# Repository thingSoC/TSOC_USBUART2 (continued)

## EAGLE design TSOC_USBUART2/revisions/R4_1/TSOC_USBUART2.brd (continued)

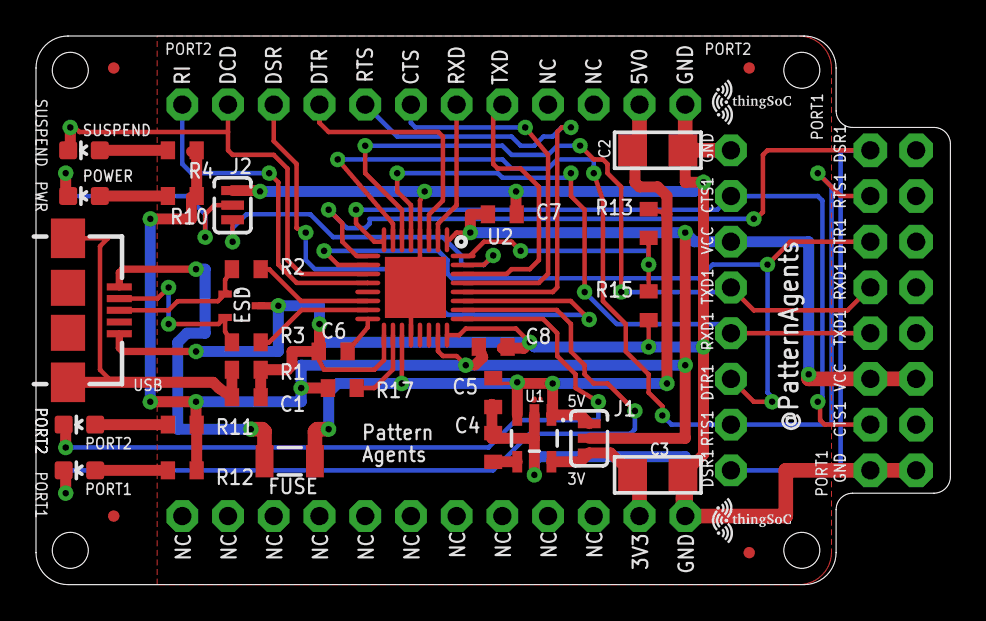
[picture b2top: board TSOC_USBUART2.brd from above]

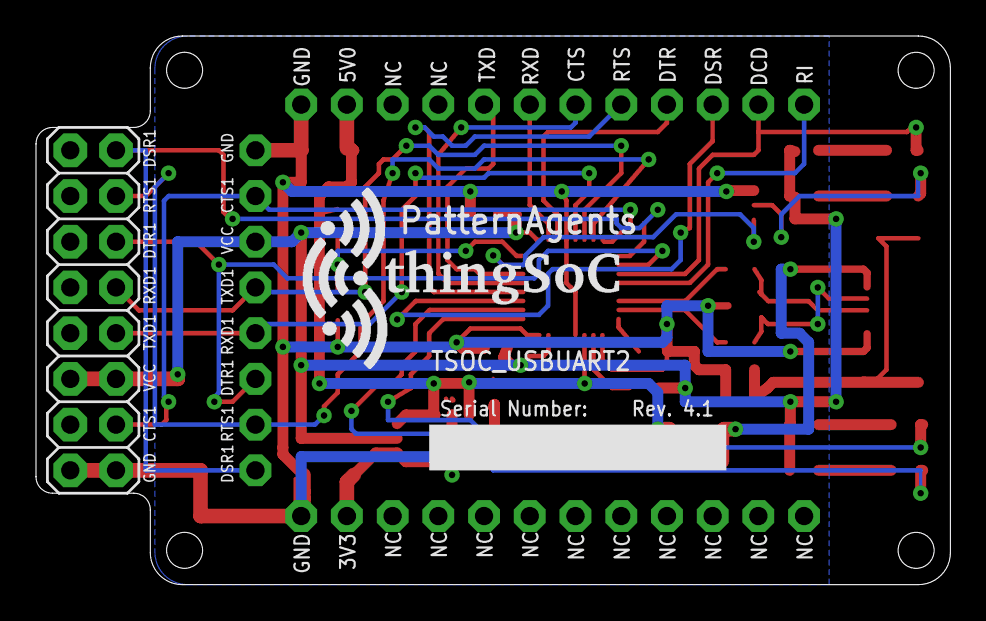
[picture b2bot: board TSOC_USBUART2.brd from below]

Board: 2 copper layers, 50.8 x 30.5 mm, 42 parts (2 on the bottom side), 36 nets.

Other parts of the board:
U$1: TSOC-LOGO-SMALL; TSOC-LOGO-SML

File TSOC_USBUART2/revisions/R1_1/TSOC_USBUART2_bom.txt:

Partlist exported from /home/moxon/github/TSOC-USBUART2/TSOC-USBUART2/TSOC_USBUART2.sch at 4/9/16 11:58 AM
Qty Value              Device             Package          Parts                  Description
1   RED                LED0603            LED-0603         SUSPEND                LEDs                                                            
1   GRN                LED0603            LED-0603         POWER                  LEDs                                                                 
1   BLUE               LED0603            LED-0603         TXD                    LEDs                          
1   YELLOW             LED0603            LED-0603         RXD                    LEDs
3   0.1uF              CAP-0603           EIA-0603         C5, C7, C8             Ceramic Capacitor SMD
1   1.0uF              CAP-0603           EIA-0603         C6                     Ceramic Capacitor SMD
2   10K                RESISTOR-0603      EIA-0603         R15, R17                                   
1   1A                 FUSE               EIA-0603         F1                     Resettable PPTC Fuse - 0603 Footptint
4   1K                 RESISTOR-0603      EIA-0603         R4, R10, R11, R12                                          
1   1M                 RESISTOR-0603      EIA-0603         R1                                                        
2   22                 RESISTOR-0603      EIA-0603         R2, R3                                                   
1   22K                RESISTOR-0603      EIA-0603         R13                                                     
2   22uF               CAP-1206           EIA-1206         C2, C3                 Ceramic Capacitor SMD           
2   470pF              CAP-0603           EIA-0603         C1, C4                 Ceramic Capacitor SMD          
1   CY7C65215-32-PROTO CY7C65215-32-PROTO QFN32-PROTO      U2                     Cypress EZ-USB ® CY7C65215-32QFN DUAL CHANNEL USB TO UART/SPI/IC Bridge
1   M08                M08                1X08-SMD-FEMALE  P1                                                                                        
1   M08PTH             M08PTH             1X08             P1A                                                                                      
1   MIC5219 3.3V       V_REG_MIC52193.3V  SOT23-5          U1                     V_REG MIC5219                                                    
1   SP1001-02JTG       SP1001-02JTG       SC70-3           ESD                    Littelfuse SP1001-02JTG TVS Diode Array 8pf 15kV 
1   USB_AB             USB_AB             USB-AB-MICRO-SMD USB                    USB AB connector

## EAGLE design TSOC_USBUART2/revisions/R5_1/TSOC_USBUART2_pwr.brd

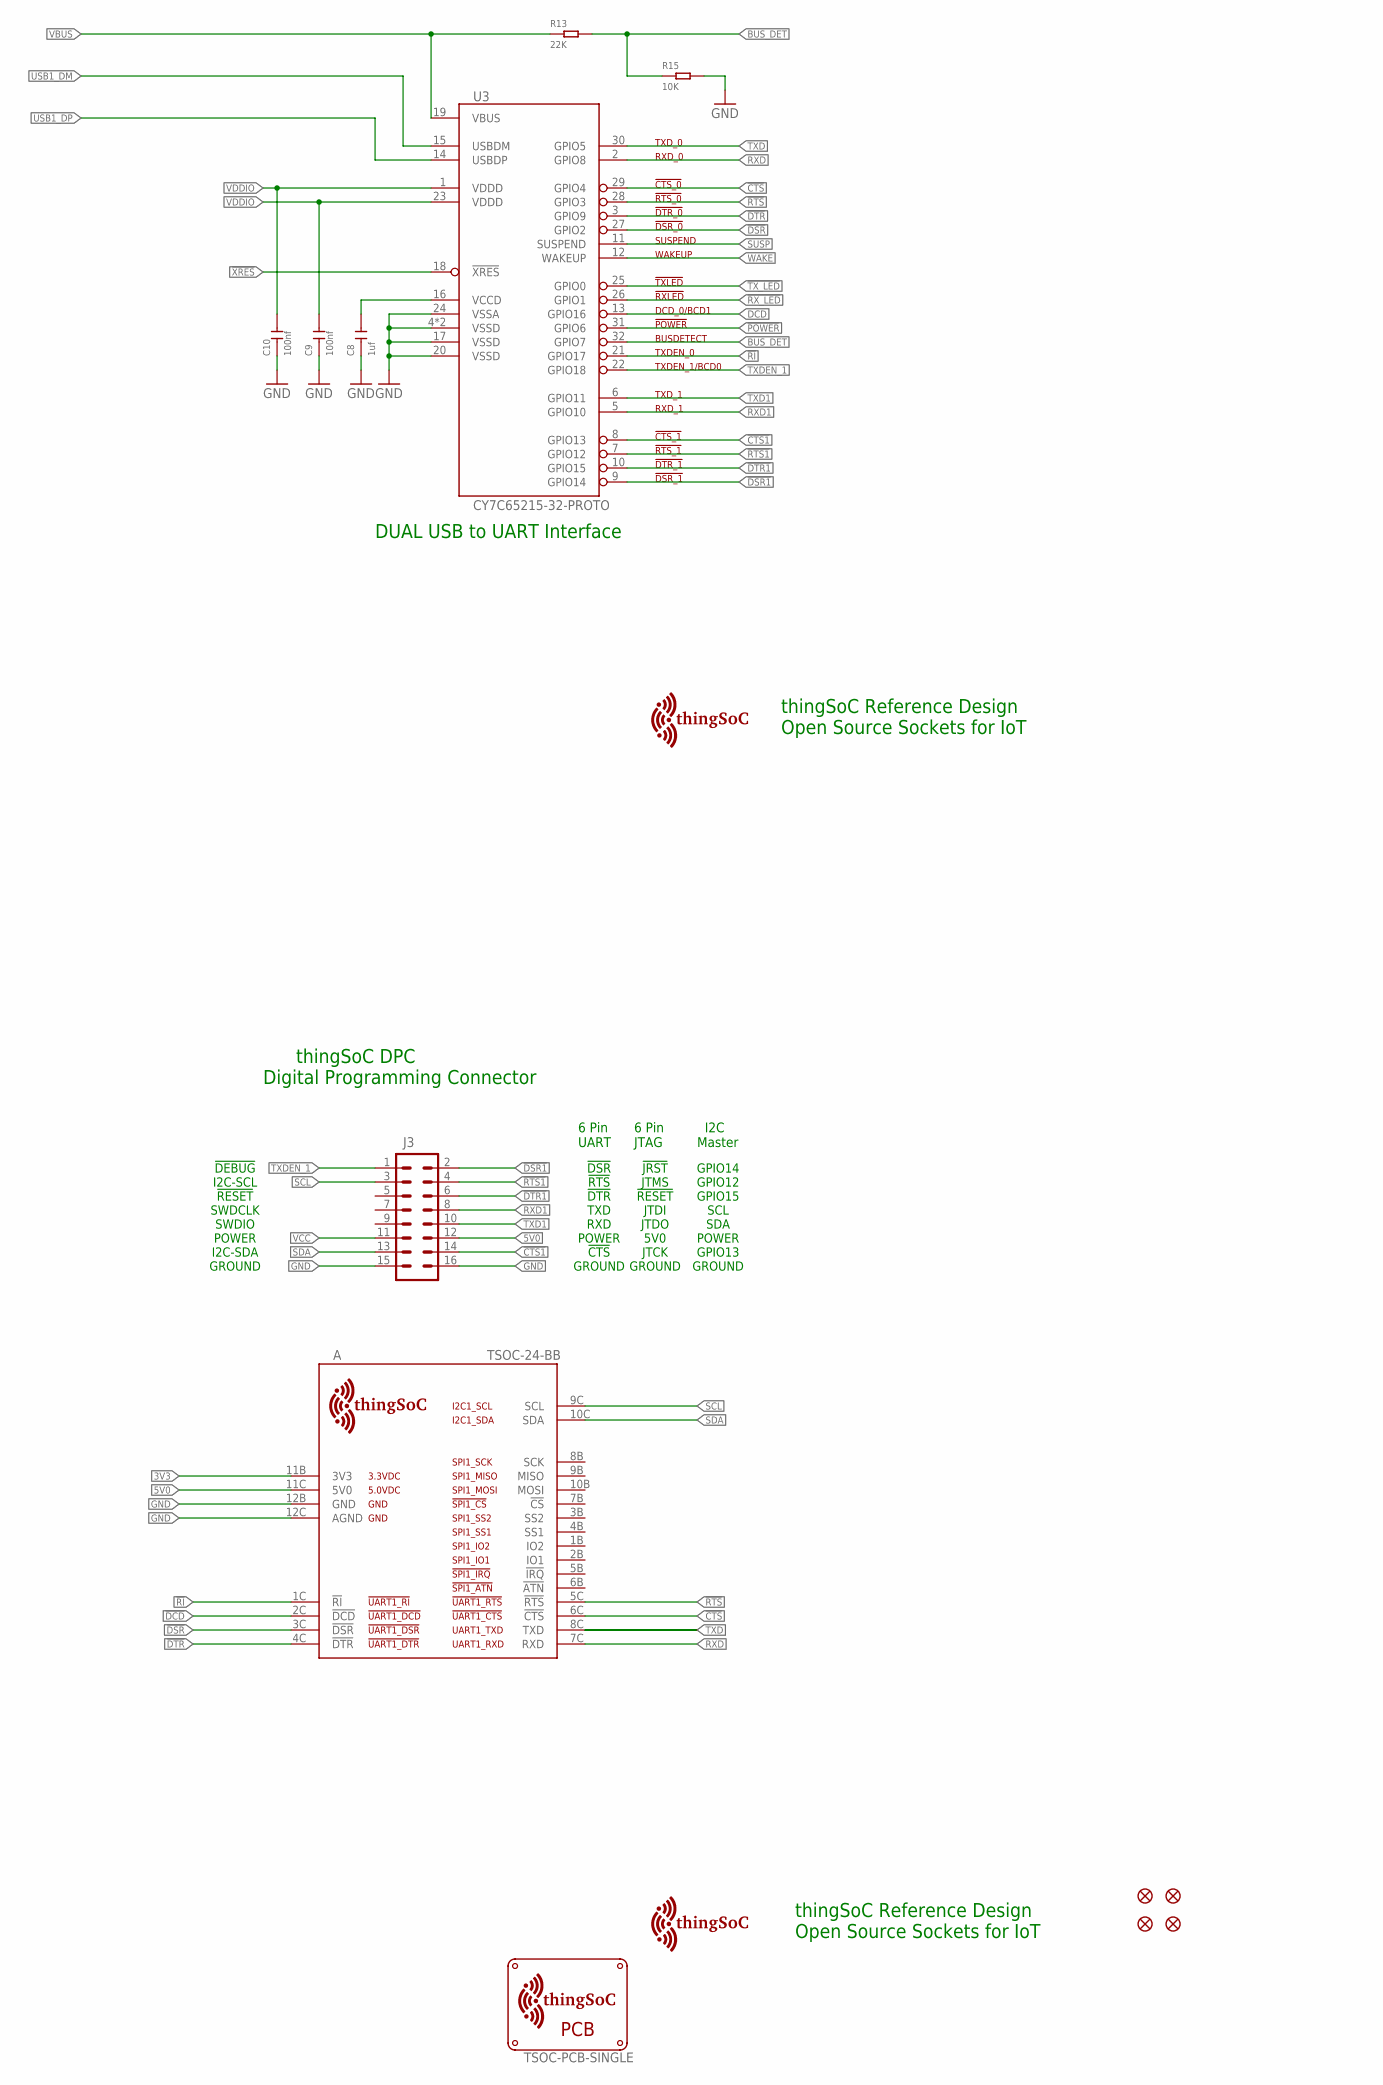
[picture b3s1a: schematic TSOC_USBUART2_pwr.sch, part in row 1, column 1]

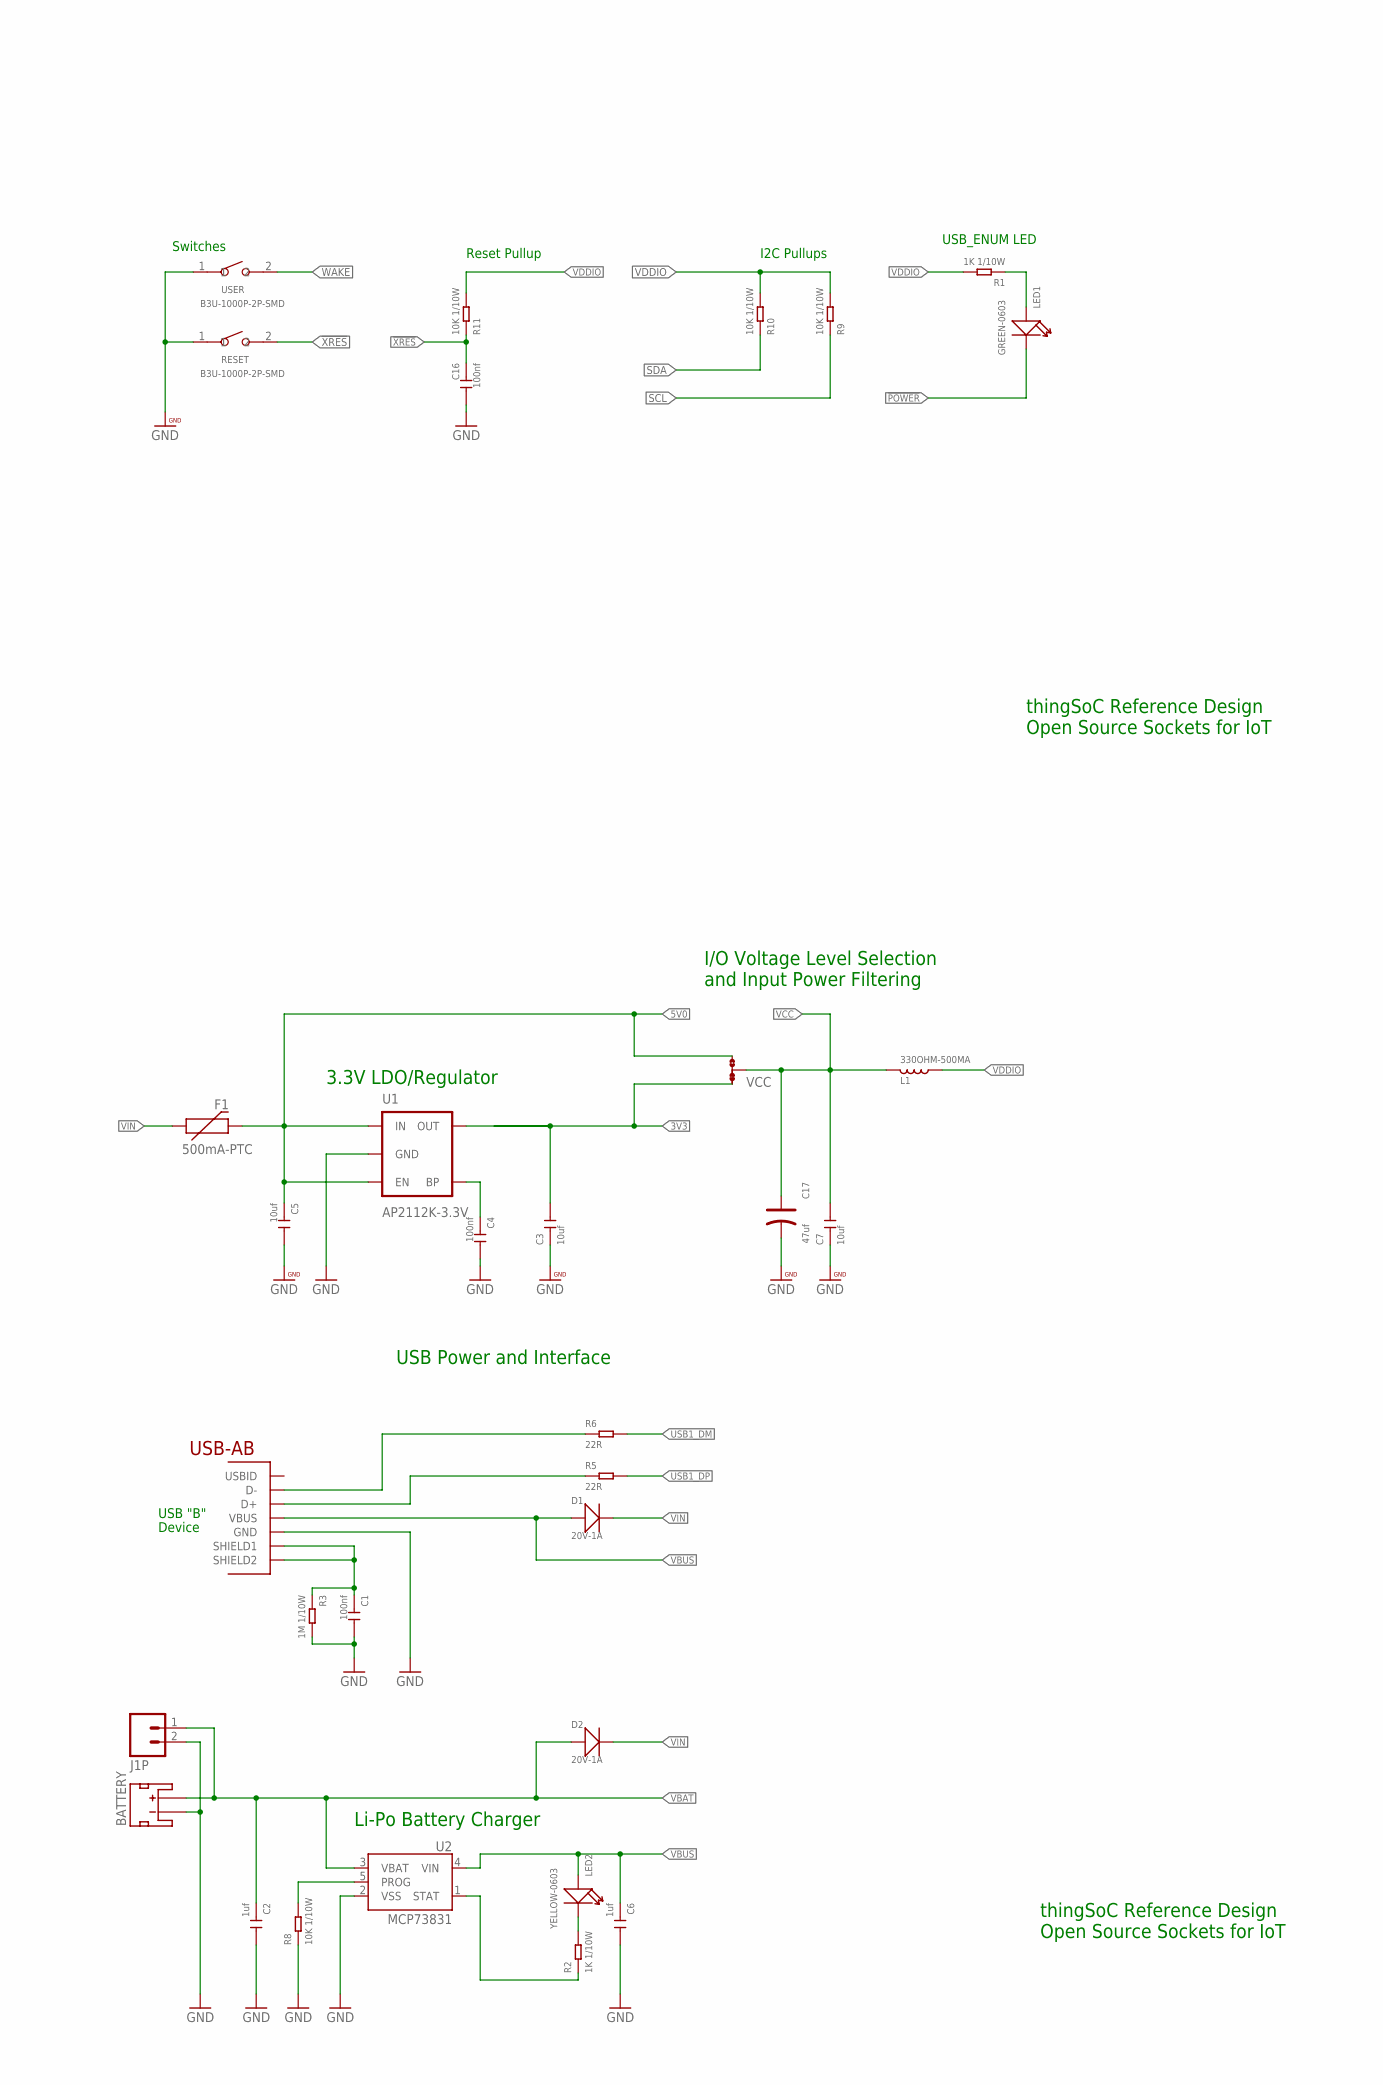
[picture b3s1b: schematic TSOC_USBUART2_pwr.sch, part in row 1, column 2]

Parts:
A: TSOC-24-BB; TSOC-BB-S24
BATTERY: JST_2MM_MALE; JST-2-SMD
C1, C4, C9, C10, C16: 100nf; C0603
C2, C6, C8: 1uf; C0603
C3, C5, C7: 10uf; C0603
C17: 47uf; AVX-A
D1, D2: 20V-1A; SOD-123
F1: 500mA-PTC; PTC-1206
FID1, FID2, FID3, FID4: FIDUCIALUFIDUCIAL; MICRO-FIDUCIAL
J1P: M02-JST-2-PTH-NO_SILK; JST-2-PTH-NS
J3: M08X2; 2X8
L1: 330OHM-500MA; L0603
LED1: GREEN-0603; LED-0603
LED2: YELLOW-0603; LED-0603
R1, R2: 1K 1/10W; R0603
R3: 1M 1/10W; R0603
R5, R6: 22R; R0603
R8, R9, R10, R11: 10K 1/10W; R0603
R13: 22K; R0603
R15: 10K; R0603
RESET: B3U-1000P-2P-SMD; SW2-2.6-3.0X2.5X1.2+0.4MM
U1: AP2112K-3.3V; SOT23-5
U2: MCP73831; SOT23-5
U3: CY7C65215-32-PROTO; QFN32-PROTO
U$1: TSOC-PCB-SINGLE; TSOC-BB-BRD-DIM
U$100: TSOC-LOGO-LRG
U$101: TSOC-LOGO-SMALL; TSOC-LOGO-SML
USB: USB_AB; USB-AB-MICRO-SMD
USER: B3U-1000P-2P-SMD; SW2-2.6-3.0X2.5X1.2+0.4MM
VCC: JMP-3-1_2

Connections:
3V3: A.11B (3V3), C3.2, U1.5 (OUT), VCC.1
5V0: A.11C (5V0), C5.1, F1.2, J3.12, U1.1 (IN), U1.3 (EN), VCC.3
!CTS: A.6C (!CTS), U3.29 (GPIO4)
!CTS1: J3.14, U3.8 (GPIO13)
!DCD: A.2C (!DCD)
!DSR: A.3C (!DSR), U3.27 (GPIO2)
!DSR1: J3.2, U3.9 (GPIO14)
!DTR: A.4C (!DTR), U3.3 (GPIO9)
!DTR1: J3.6, U3.10 (GPIO15)
!POWER: LED1.-, U3.31 (GPIO6)
!RI: A.1C (!RI), U3.21 (GPIO17)
!RTS: A.5C (!RTS), U3.28 (GPIO3)
!RTS1: J3.4, U3.7 (GPIO12)
!RX_LED: U3.26 (GPIO1)
!TX_LED: U3.25 (GPIO0)
!XRES: C16.1, R11.1, RESET.2, U3.18 (!XRES)
BUS_DET: R13.2, R15.1, U3.32 (GPIO7)
BYPASS1: C4.1, U1.4 (BP)
CLED: LED2.-, R2.2
CSTAT: R2.1, U2.1 (STAT)
DCD: U3.13 (GPIO16)
GND: A.12B (GND), A.12C (AGND), BATTERY.1 (-), C1.2, C2.2, C3.1, C4.2, C5.2, C6.2, C7.1, C8.1, C9.1, C10.1, C16.2, C17.-, J1P.2, J3.15, J3.16, R3.2, R8.1, R15.2, RESET.1, U1.2 (GND), U2.2 (VSS), U3.4 (VSSD), U3.17 (VSSD), U3.20 (VSSD), U3.24 (VSSA), U3.EXP (VSSD), USB.GND, USER.1
unnamed: R8.2, U2.5 (PROG)
unnamed: LED1.+, R1.1
RXD: A.7C (RXD), U3.2 (GPIO8)
RXD1: J3.8, U3.5 (GPIO10)
SCL: A.9C (SCL), J3.3, R9.1
SDA: A.10C (SDA), J3.13, R10.1
SUSP: U3.11 (SUSPEND)
TXD: A.8C (TXD), U3.30 (GPIO5)
TXD1: J3.10, U3.6 (GPIO11)
TXDEN_1: J3.1, U3.22 (GPIO18)
USB1_DM: R6.2, U3.15 (USBDM)
USB1_DP: R5.2, U3.14 (USBDP)
USB1_M: R6.1, USB.D-
USB1_P: R5.1, USB.D+
USB1_SHIELD: C1.1, R3.1, USB.SHIELD1, USB.SHIELD2
VBAT: BATTERY.2 (+), C2.1, D2.+, J1P.1, U2.3 (VBAT)
VBUS: C6.1, D1.+, LED2.+, R13.1, U2.4 (VIN), U3.19 (VBUS), USB.VBUS
VCC: C7.2, C17.+, J3.11, L1.1, VCC.2
VCCD1: C8.2, U3.16 (VCCD)
VDDIO: C9.2, C10.2, L1.2, R1.2, R9.2, R10.2, R11.2, U3.1 (VDDD), U3.23 (VDDD)
VIN: D1.-, D2.-, F1.1
WAKE: U3.12 (WAKEUP), USER.2

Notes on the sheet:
USB "B"
Device
3.3V LDO/Regulator
Reset Pullup
USB_ENUM LED
Li-Po Battery Charger
USB Power and Interface
I/O Voltage Level Selection and Input Power Filtering
I2C Pullups
thingSoC Reference Design Open Source Sockets for IoT
thingSoC DPC Digital Programming Connector
Switches
DUAL USB to UART Interface
I2C-SDA
I2C-SCL
!RESET
SWDCLK
SWDIO
POWER
GROUND
!DEBUG
!DSR
!RTS
!CTS
!DTR
TXD
RXD
!JRST
JTMS
JTCK
JTDI
JTDO
5V0
6 Pin UART
6 Pin JTAG
I2C Master
GPIO14
GPIO12
GPIO13
GPIO15

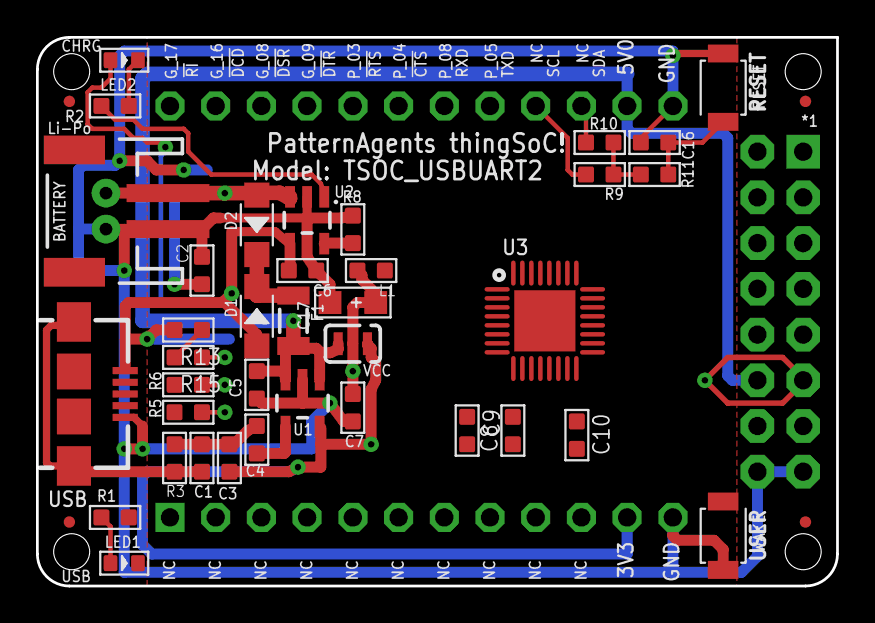
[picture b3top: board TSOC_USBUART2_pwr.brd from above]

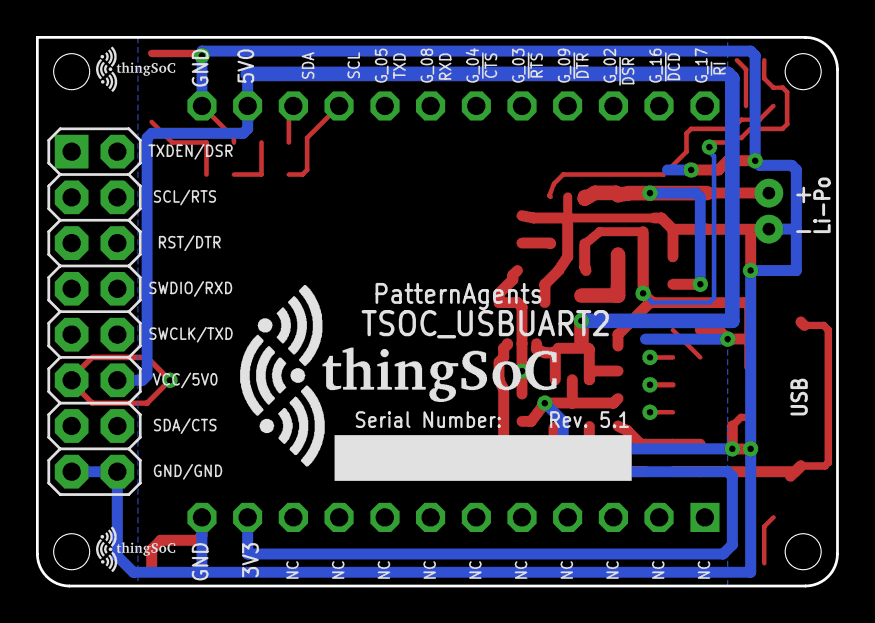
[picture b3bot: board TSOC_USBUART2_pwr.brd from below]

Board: 2 copper layers, 44.5 x 30.5 mm, 48 parts (5 on the bottom side), 39 nets.

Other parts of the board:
U$102: TSOC-LOGO-SMALL; TSOC-LOGO-SML

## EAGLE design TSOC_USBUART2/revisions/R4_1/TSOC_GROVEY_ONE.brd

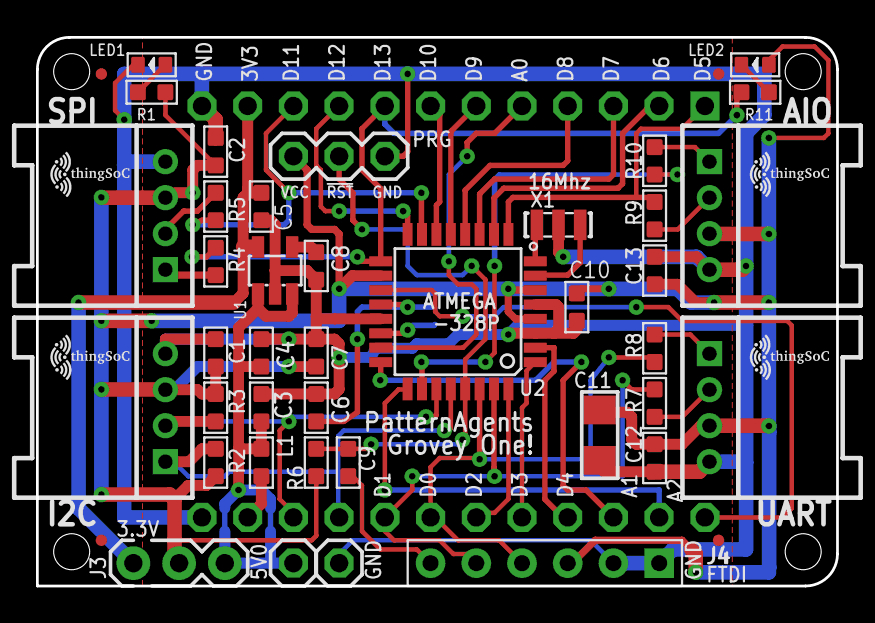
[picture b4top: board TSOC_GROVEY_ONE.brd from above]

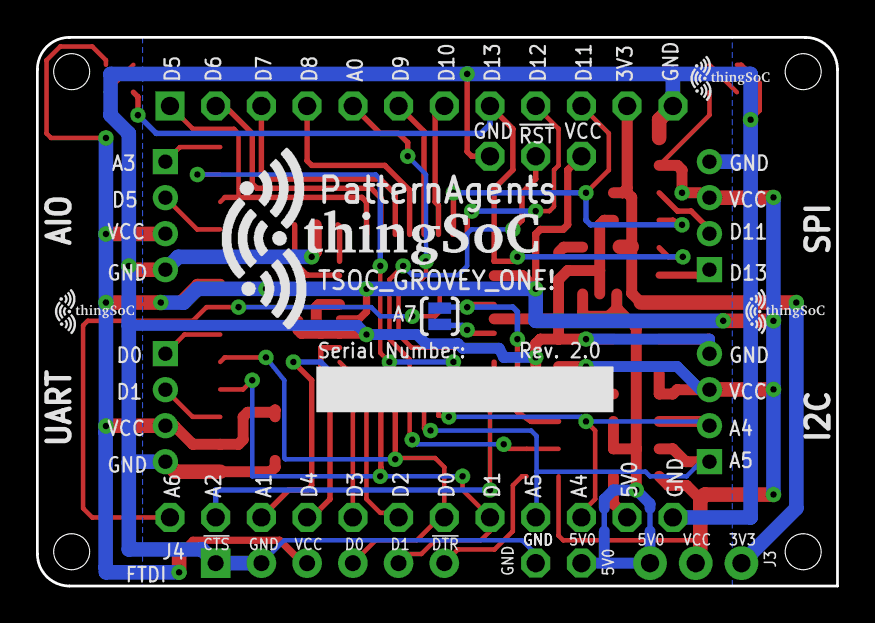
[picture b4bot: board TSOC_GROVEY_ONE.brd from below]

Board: 2 copper layers, 44.5 x 30.5 mm, 54 parts (5 on the bottom side), 41 nets.

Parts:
5V0: 1X01
$$U$1: TSOC-PCB-SINGLE; TSOC-BB-BRD-DIM
$$U$2, $$U$3: TSOC-LOGO-SMALL; TSOC-LOGO-SML
A7: JMP-2-NO
AIO: 4P-2.0-90D; HW4-2.0-90D
C1, C2, C4, C6, C7, C9, C10, C12, C13: 100nf; C0603
C3, C5: 10uf; C0603
C8: 470Pf; C0603
C11: 22uF; EIA-1206
FID1, FID2, FID3, FID4: FIDUCIALUFIDUCIAL; MICRO-FIDUCIAL
GND: 1X01
I2C: 4P-2.0-90D; HW4-2.0-90D
J3: NO; JMP-3-NO-PTH-2.54
J4: 6p-2.54; H6-2.54
L1: 120OHM-500MA; L0603
LED1: GREEN-0603; LED-0603
LED2: RED-0603; LED-0603
PRG: 1X03
R1, R4, R5, R7, R8, R9, R10, R11: 1K 1/10W; R0603
R2, R3: 2.2K; R0603
R6: 10K 1/10W; R0603
SPI: 4P-2.0-90D; HW4-2.0-90D
TSOC: TSOC-24-BB; TSOC-BB-S24
U1: XC6204B332MR-SOT23-5; SOT-23-5
U2: ATMEGA328; TQFP32-08
U$1, U$3, U$100, U$101, U$103: TSOC-LOGO-SMALL; TSOC-LOGO-SML
U$102: TSOC-LOGO-LRG
UART: 4P-2.0-90D; HW4-2.0-90D
X1: 16MHZ; X3-SMD-3.6X1.3X0.8MM

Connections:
3V3: C5.2, J3.1, TSOC.11B, U1.5
5V0: 5V0.1, C3.2, C4.1, J3.3, L1.1, U1.1, U1.3
!JRST: C9.1, J4.6
!RST: C9.2, PRG.2, R6.1, U2.29
A0: TSOC.5B, U2.23
A1: TSOC.3C, U2.24
A2: TSOC.2C, U2.25
A3: R10.1, U2.26
A3E: AIO.1, R10.2
A4: I2C.2, R3.1, TSOC.10C, U2.27
A5: I2C.1, R2.1, TSOC.9C, U2.28
A6: TSOC.1C, U2.19
A7: A7.1, U2.22
AREF: A7.2, C6.2, U2.20
BYPASS1: C8.1, U1.4
D0: J4.4, R8.1, TSOC.7C, U2.30
D0E: R8.2, UART.1
D1: J4.5, R7.1, TSOC.8C, U2.31
D1E: R7.2, UART.2
D2: TSOC.6C, U2.32
D3: TSOC.5C, U2.1
D4: TSOC.4C, U2.2
D5: R9.1, TSOC.1B, U2.9
D5E: AIO.2, R9.2
D6: TSOC.2B, U2.10
D7: TSOC.3B, U2.11
D8: TSOC.4B, U2.12
D9: TSOC.6B, U2.13
D10: TSOC.7B, U2.14
D11: R5.2, TSOC.10B, U2.15
D11E: R5.1, SPI.2
D12: TSOC.9B, U2.16
D13: R4.2, R11.2, TSOC.8B, U2.17
D13E: R4.1, SPI.1
GND: AIO.4, C1.2, C2.2, C3.1, C4.2, C5.1, C6.1, C7.1, C8.2, C10.1, C11.2, C12.2, C13.2, GND.1, I2C.4, J4.1, J4.2, LED1.-, PRG.3, SPI.4, TSOC.12B, TSOC.12C, U1.2, U2.3, U2.5, U2.21, UART.4, X1.2
LEDR: LED2.-, R11.1
unnamed: LED1.+, R1.1
TSOC_5V0: L1.2, TSOC.11C
VCC: AIO.3, C1.1, C2.1, C7.2, C10.2, C11.1, C12.1, C13.1, I2C.3, J3.2, J4.3, LED2.+, PRG.1, R1.2, R2.2, R3.2, R6.2, SPI.3, U2.4, U2.6, U2.18, UART.3
XIN: U2.7, X1.3
XOUT: U2.8, X1.1

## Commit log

2016-05-23 update borad outline
2016-07-10 update to V4_0
2016-07-22 update hole placements
2016-08-08 add product images
2017-01-14 update R5
2017-01-16 update documetation
